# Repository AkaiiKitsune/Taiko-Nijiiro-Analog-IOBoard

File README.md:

# Analog Taiko IO Board - ESP32 S3 DevkitC1

**PLEASE NOTE THAT THIS DESIGN IS FLAWED AND NEEDS TO BE REDONE!**  
While it will work, this has massive noise issues and is currently not ready for use.

Open-source project to make your own Taiko no Tatsujin IO Board for PC use or SD cabs converted to Nijiiro.  
It emulates an analog joystick to enable force sensing, just like how you would play on an official arcade machine.

## Table of content

- [Analog Taiko IO Board - ESP32 S3 DevkitC1](#analog-taiko-io-board---esp32-s3-devkitc1)
  - [Table of content](#table-of-content)
  - [About this Project](#about-this-project)
  - [Components needed](#components-needed)
  - [Parameters tuning](#parameters-tuning)
    - [Player Selection](#player-selection)
    - [Sensitivity](#sensitivity)
  - [Additional Notes](#additional-notes)
    - [Why bridge rectifiers](#why-bridge-rectifiers)
    - [TaikoArcadeLoader](#taikoarcadeloader)

## About this Project

This is a hard fork of [ShikyC's](https://github.com/ShikyC/Taiko-Drum-Controller-Arduino) taiko controller project with some QOL improvements.  
It's aim is to provide accurate-enough arcade drum support for converted SD cabs or bootlegs running Taiko Nijiiro.

**This program is for personal and non-commercial use only.**

## Components needed

* An [ESP32 S3 DevKitC-1](https://docs.espressif.com/projects/esp-idf/en/stable/esp32s3/hw-reference/esp32s3/user-guide-devkitc-1.html) board.
* 4 [JST PH 2.0](https://fr.aliexpress.com/item/1005004067623293.html) connectors (i'm using 90° ones but straight ones work too).
* 4 [1206 LEDs](https://fr.aliexpress.com/item/1005005975741298.html) (2 Blue and 2 Red).
* 8 1206 100kΩ resistors.
* 4 bridge rectifier chips. This project uses [DB107S](https://www.rectron.com/public/product_datasheets/db101s-db107s.pdf) (see the Additional Notes section for details).
* 4 10k variable resistors. This project uses [3362P-1-103](https://www.mouser.fr/datasheet/2/54/3362-776956.pdf)

All of those parts can be found for next to nothing on aliexpress.

You'll also need an IO Board PCB (you can find the gerber files in [here](PCB/Export/)).
I've used [JLCPCB](https://jlcpcb.com/) to order mine.

## Parameters tuning

All the parameters are located in [params.h](Firmware/params.h).

### Player Selection

   By setting `#define PLAYER_SELECT` to either `1` or `2`, you can set what player the board will act as. If you're using two of these, make sure that they each are set to a different player to avoid issues.

   The buildin led of the ESP32 S3 DevKitC1 will be either red or blue depending on that value !

### Sensitivity

   Not all piezoelectric sensors are the same, and thus the captured signals from the 4 sensors may vary significantly. The sensitivity adjust trims are used to normalize those differences.  

   To facilitate setting those trims up, set `DEBUG` to `1`, flash the firmware, roll on one of the 4 areas of the drum, and visualize the graph from the output of the Serial Plotter.

   In the following example, the right-don area generates a much higher value than other 3, so you can adjust the `sensitivity` by turning the R_DON potentiometer to eliminate the issue.

   Note that the installation of the sensors is critical. You should make sure that the sensors are firmly attached on the wood and located properly, as seen on the picture below.

## Additional Notes

### Why bridge rectifiers

   Without biasing the voltage of the piezoelectric sensors, their output voltage range is about -5V to +5V. However, the ESP32 ADCs only accept positive voltage values from 0 to 3.3V. When they receive a negative voltage, it's simply truncated to 0.

   In a taiko drum, all the 4 vibrating pieces are connected together, meaning that if you hit left-don, the processor also receives signals from left-kat, right-don, and right-kat. If the left-don piezoelectric sensor generates a negative voltage at the beginning and is truncated by the ADC, it will cause a minor "delay" of about 3 to 4 milliseconds, and the processor could incorrectly treat this hit as a right-don, a left-kat, or even a right-kat, whichever sends a highest positive value.

   Using a bridge rectifier, all negative values are converted to positive. In other words, it's acting like a mathematical `abs()` function, ensuring that we don't miss any negative voltages.

### TaikoArcadeLoader

You'll need to use a recent version of esuo1198's fork of [TaikoArcadeLoader](https://github.com/esuo1198/TaikoArcadeLoader) (Commit [945e104](https://github.com/esuo1198/TaikoArcadeLoader/commit/945e104) and up).

Open `config.toml` and enable analog input like so :

```toml
   [controller]
   analog = true  
```

If the IO Board is detected but your game doesn't register any inputs, check in `gamecontrollerdb.txt` that you have the following entry under `#Windows`:

`030052a8694800006948000000000000,Nijiiro Analog IO Board,-leftx:-a0,+leftx:+a0,-lefty:-a1,+lefty:+a1,-rightx:-a2,+rightx:+a2,-righty:-a3,+righty:+a3,platform:Windows,`

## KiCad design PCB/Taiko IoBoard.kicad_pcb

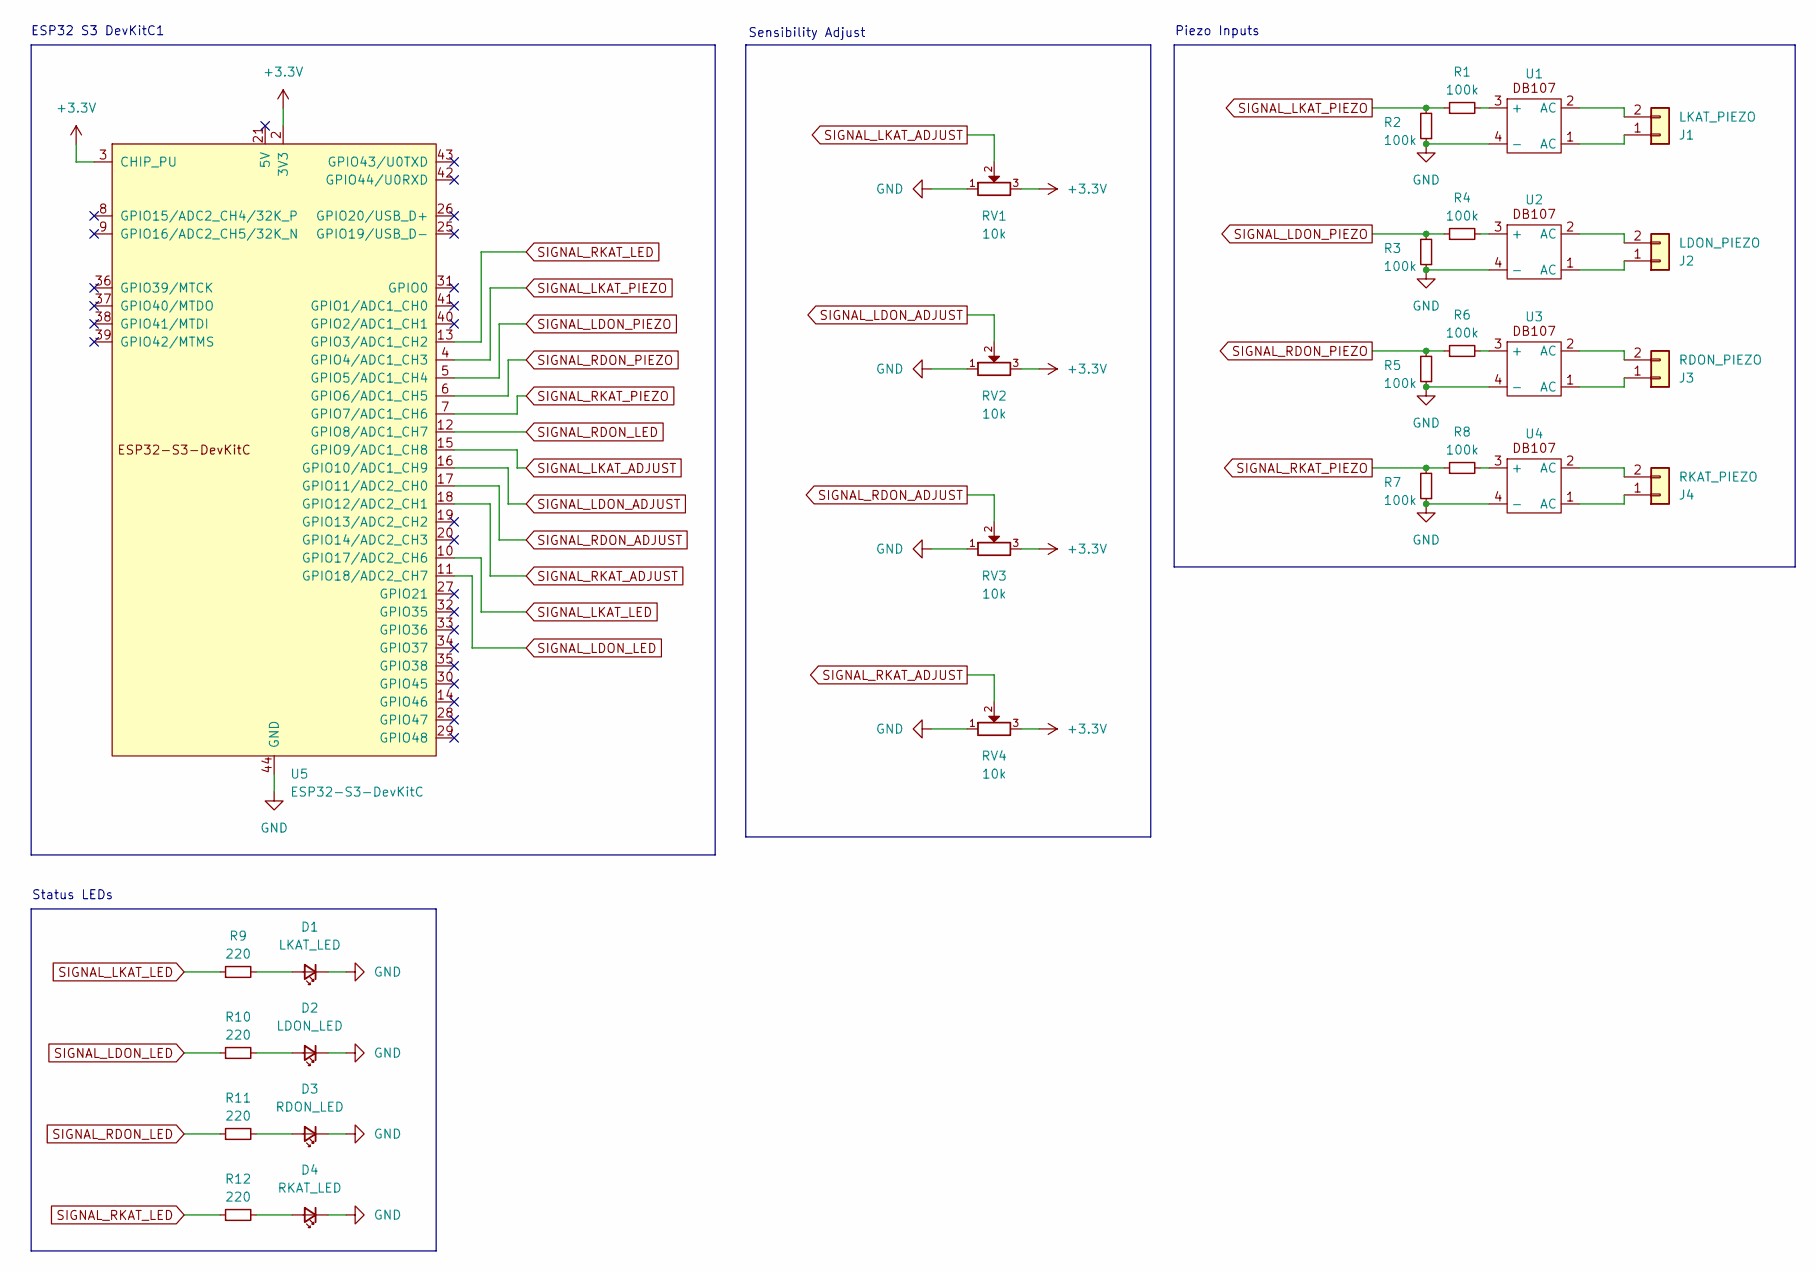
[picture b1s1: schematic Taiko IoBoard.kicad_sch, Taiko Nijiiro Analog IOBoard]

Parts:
D1: LKAT_LED; LED_1206_3216Metric_Pad1.42x1.75mm_HandSolder
D2: LDON_LED; LED_1206_3216Metric_Pad1.42x1.75mm_HandSolder
D3: RDON_LED; LED_1206_3216Metric_Pad1.42x1.75mm_HandSolder
D4: RKAT_LED; LED_1206_3216Metric_Pad1.42x1.75mm_HandSolder
J1: LKAT_PIEZO; TE_440055-2_1x02_P2.00mm_Horizontal
J2: LDON_PIEZO; TE_440055-2_1x02_P2.00mm_Horizontal
J3: RDON_PIEZO; TE_440055-2_1x02_P2.00mm_Horizontal
J4: RKAT_PIEZO; TE_440055-2_1x02_P2.00mm_Horizontal
R1, R2, R3, R4, R5, R6, R7, R8: 100k; R_1206_3216Metric_Pad1.30x1.75mm_HandSolder
R9, R10, R11, R12: 220; R_1206_3216Metric_Pad1.30x1.75mm_HandSolder
RV1, RV2, RV3, RV4: 10k; potentiometer_3362P
U1, U2, U3, U4: DB10X SOP4
U5: ESP32-S3-DevKitC

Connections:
+3.3V: RV1.3, RV2.3, RV3.3, RV4.3, U5.1 (3V3), U5.2 (3V3), U5.3 (CHIP_PU)
GND: D1.1 (K), D2.1 (K), D3.1 (K), D4.1 (K), R2.1, R3.1, R5.1, R7.1, RV1.1, RV2.1, RV3.1, RV4.1, U1.4 (-), U2.4 (-), U3.4 (-), U4.4 (-), U5.22 (GND), U5.23 (GND), U5.24 (GND), U5.44 (GND)
unnamed: D1.2 (A), R9.2
unnamed: D2.2 (A), R10.2
unnamed: D3.2 (A), R11.2
unnamed: D4.2 (A), R12.2
unnamed: J1.1, U1.1 (AC)
unnamed: J1.2, U1.2 (AC)
unnamed: J2.1, U2.1 (AC)
unnamed: J2.2, U2.2 (AC)
unnamed: J3.1, U3.1 (AC)
unnamed: J3.2, U3.2 (AC)
unnamed: J4.1, U4.1 (AC)
unnamed: J4.2, U4.2 (AC)
unnamed: R1.2, U1.3 (+)
unnamed: R4.2, U2.3 (+)
unnamed: R6.2, U3.3 (+)
unnamed: R8.2, U4.3 (+)
SIGNAL_LDON_ADJUST: RV2.2, U5.16 (GPIO10/ADC1_CH9)
SIGNAL_LDON_LED: R10.1, U5.11 (GPIO18/ADC2_CH7)
SIGNAL_LDON_PIEZO: R3.2, R4.1, U5.5 (GPIO5/ADC1_CH4)
SIGNAL_LKAT_ADJUST: RV1.2, U5.15 (GPIO9/ADC1_CH8)
SIGNAL_LKAT_LED: R9.1, U5.10 (GPIO17/ADC2_CH6)
SIGNAL_LKAT_PIEZO: R1.1, R2.2, U5.4 (GPIO4/ADC1_CH3)
SIGNAL_RDON_ADJUST: RV3.2, U5.17 (GPIO11/ADC2_CH0)
SIGNAL_RDON_LED: R11.1, U5.12 (GPIO8/ADC1_CH7)
SIGNAL_RDON_PIEZO: R5.2, R6.1, U5.6 (GPIO6/ADC1_CH5)
SIGNAL_RKAT_ADJUST: RV4.2, U5.18 (GPIO12/ADC2_CH1)
SIGNAL_RKAT_LED: R12.1, U5.13 (GPIO3/ADC1_CH2)
SIGNAL_RKAT_PIEZO: R7.2, R8.1, U5.7 (GPIO7/ADC1_CH6)

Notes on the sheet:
ESP32 S3 DevKitC1
Sensibility Adjust
Piezo Inputs
Status LEDs

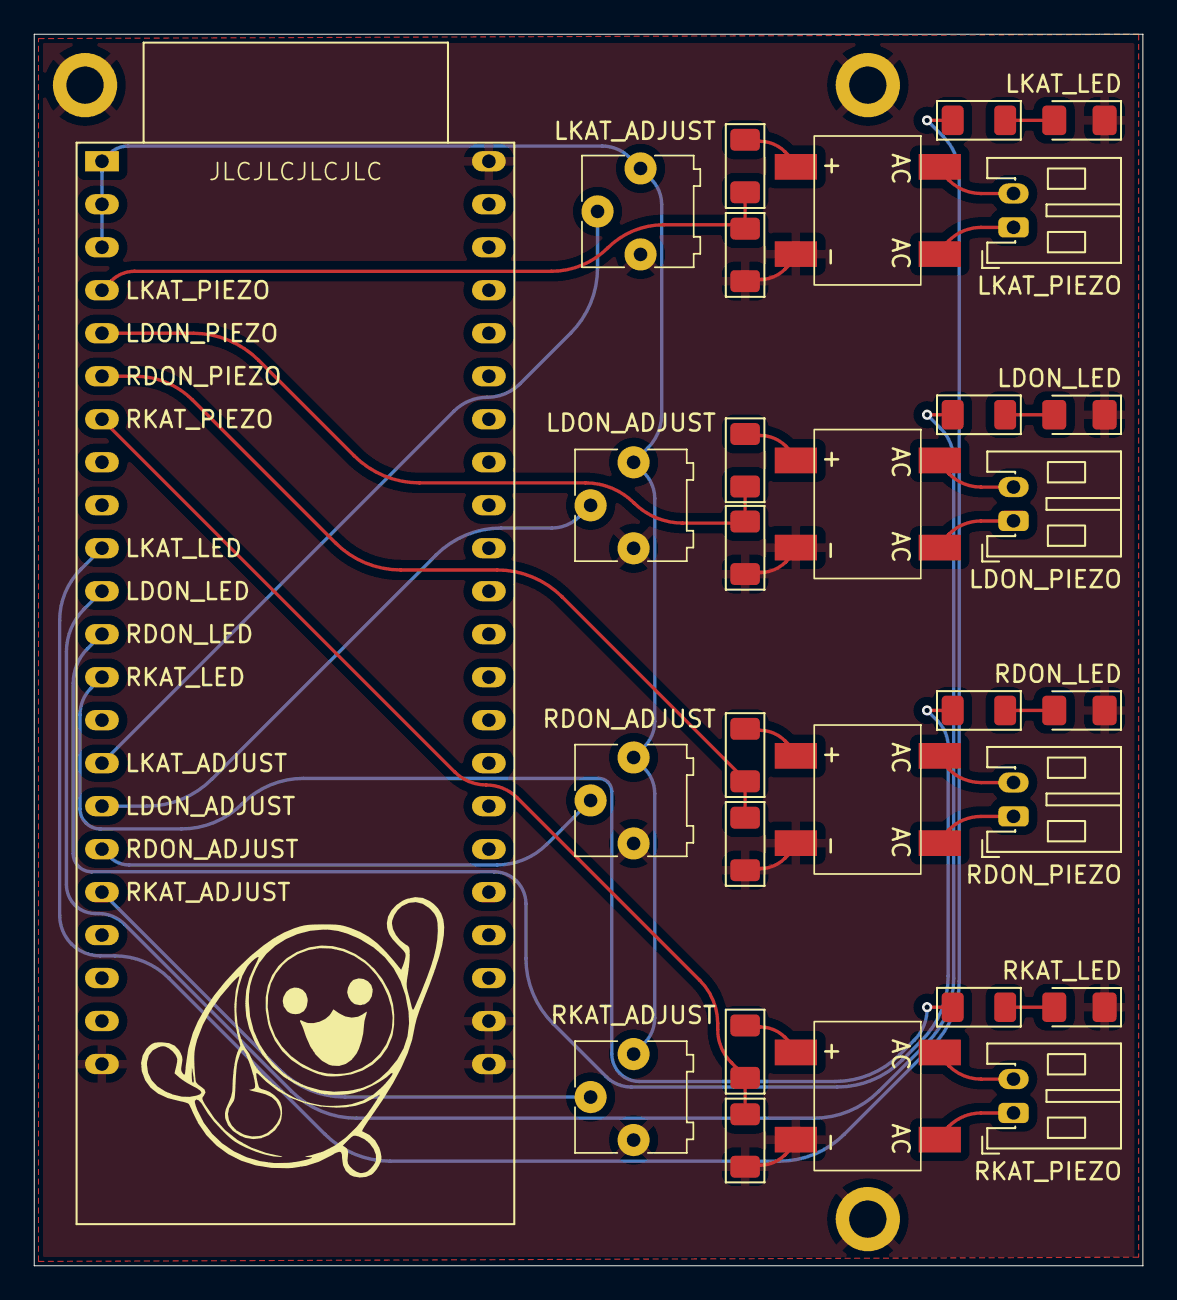
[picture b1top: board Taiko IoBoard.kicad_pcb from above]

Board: 2 copper layers, 65.5 x 72.8 mm, 29 parts (0 on the bottom side), 30 nets.

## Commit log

2024-04-30 Hard fork initial commit
    This commit contains the kicad files for the PCB, the updated firmware for this new pcb design.
2024-04-30 Fixed links
2024-04-30 Added table of content, fixed readme syntax
2024-10-24 Actualiser README.md
